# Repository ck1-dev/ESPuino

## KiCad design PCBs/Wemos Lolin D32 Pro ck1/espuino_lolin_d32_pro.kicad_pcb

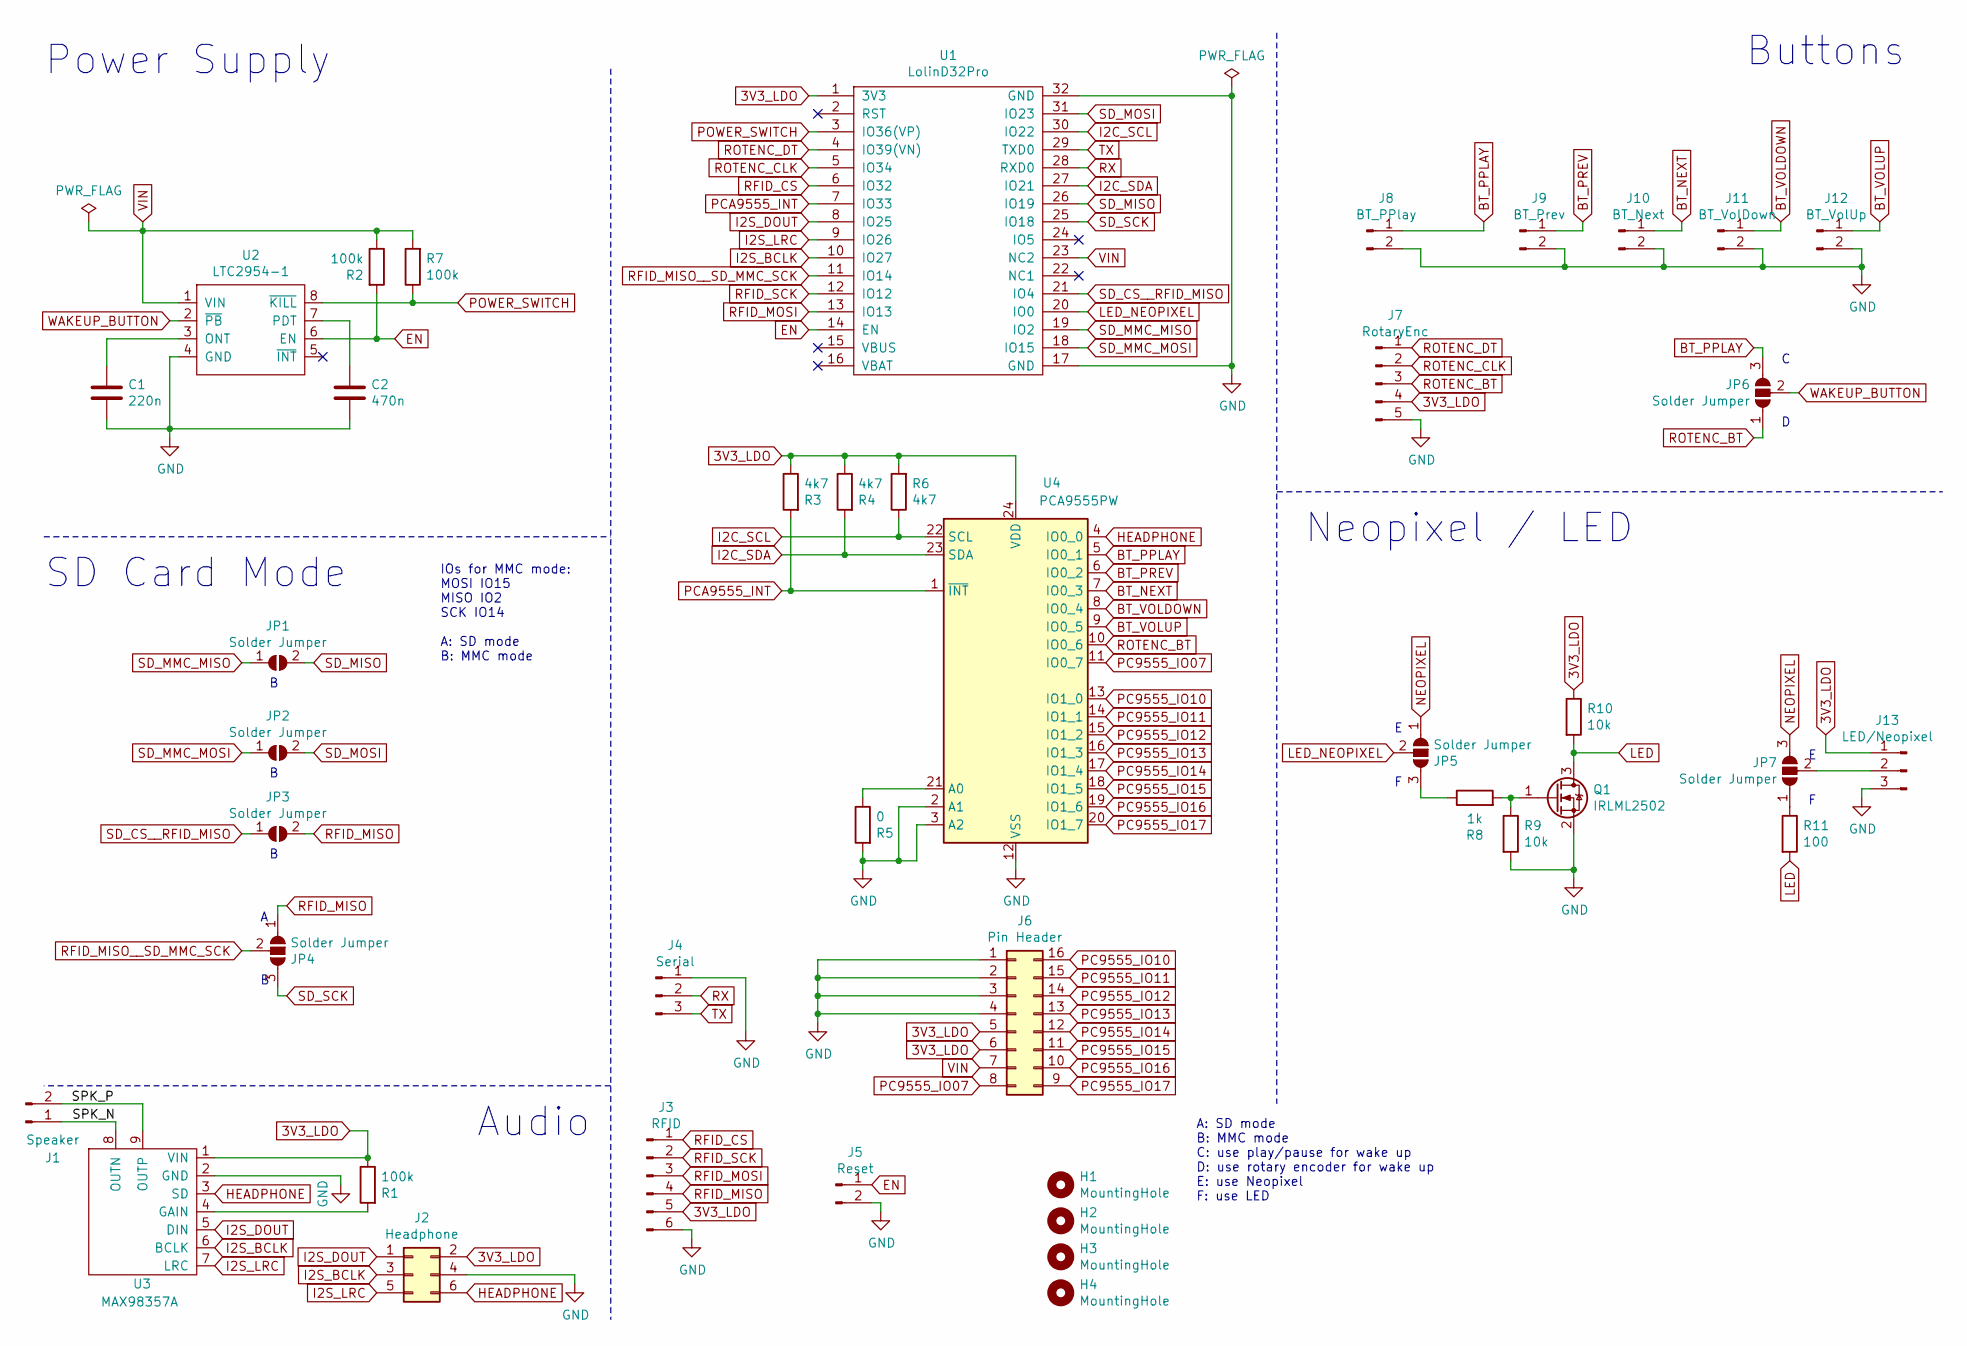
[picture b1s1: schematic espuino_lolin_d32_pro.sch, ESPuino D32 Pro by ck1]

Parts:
C1: 220n; C_0805_2012Metric_Pad1.18x1.45mm_HandSolder
C2: 470n; C_0805_2012Metric_Pad1.18x1.45mm_HandSolder
H1, H2, H3, H4: MountingHole; MountingHole_3mm
J1: Speaker; JST_PH_B2B-PH-K_1x02_P2.00mm_Vertical
J2: Headphone; IDC-Header_2x03_P2.54mm_Vertical
J3: RFID; JST_PH_B6B-PH-K_1x06_P2.00mm_Vertical
J4: Serial; PinHeader_1x03_P2.54mm_Vertical
J5: Reset; JST_PH_B2B-PH-K_1x02_P2.00mm_Vertical
J6: Pin Header; PinHeader_2x08_P2.54mm_Vertical
J7: RotaryEnc; JST_PH_B5B-PH-K_1x05_P2.00mm_Vertical
J8: BT_PPlay; JST_PH_B2B-PH-K_1x02_P2.00mm_Vertical
J9: BT_Prev; JST_PH_B2B-PH-K_1x02_P2.00mm_Vertical
J10: BT_Next; JST_PH_B2B-PH-K_1x02_P2.00mm_Vertical
J11: BT_VolDown; JST_PH_B2B-PH-K_1x02_P2.00mm_Vertical
J12: BT_VolUp; JST_PH_B2B-PH-K_1x02_P2.00mm_Vertical
J13: LED/Neopixel; JST_PH_B3B-PH-K_1x03_P2.00mm_Vertical
JP1, JP2, JP3: Solder Jumper; SolderJumper-2_P1.3mm_Open_Pad1.0x1.5mm
JP4, JP5, JP6, JP7: Solder Jumper; SolderJumper-3_P1.3mm_Open_Pad1.0x1.5mm
Q1: IRLML2502; SOT-23
R1, R2, R7: 100k; R_0805_2012Metric_Pad1.20x1.40mm_HandSolder
R3, R4, R6: 4k7; R_0805_2012Metric_Pad1.20x1.40mm_HandSolder
R5: 0; R_0805_2012Metric_Pad1.20x1.40mm_HandSolder
R8: 1k; R_0805_2012Metric_Pad1.20x1.40mm_HandSolder
R9, R10: 10k; R_0805_2012Metric_Pad1.20x1.40mm_HandSolder
R11: 100; R_0805_2012Metric_Pad1.20x1.40mm_HandSolder
U1: LolinD32Pro; Lolin_D32_PRO
U2: LTC2954-1; TSOT-23-8
U3: MAX98357A
U4: PCA9555PW; TSSOP-24_4.4x7.8mm_P0.65mm

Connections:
3V3_LDO: J2.2, J3.5, J6.5, J6.6, J7.4, J13.1, R1.1, R3.1, R4.1, R6.2, R10.1, U1.1 (3V3), U3.1 (VIN), U4.24 (VDD)
/SPK_N: J1.1, U3.8 (OUTN)
/SPK_P: J1.2, U3.9 (OUTP)
BT_NEXT: J10.1, U4.7 (IO0_3)
BT_PPLAY: J8.1, JP6.3 (B), U4.5 (IO0_1)
BT_PREV: J9.1, U4.6 (IO0_2)
BT_VOLDOWN: J11.1, U4.8 (IO0_4)
BT_VOLUP: J12.1, U4.9 (IO0_5)
EN: J5.1, R2.2, U1.14 (EN), U2.6 (EN)
GND: C1.2, C2.2, J2.4, J3.6, J4.1, J5.2, J6.1, J6.2, J6.3, J6.4, J7.5, J8.2, J9.2, J10.2, J11.2, J12.2, J13.3, Q1.2 (S), R5.2, R9.2, U1.17 (GND), U1.32 (GND), U2.4 (GND), U3.2 (GND), U4.2 (A1), U4.3 (A2), U4.12 (VSS)
HEADPHONE: J2.6, U3.3 (SD), U4.4 (IO0_0)
I2C_SCL: R6.1, U1.30 (IO22), U4.22 (SCL)
I2C_SDA: R4.2, U1.27 (IO21), U4.23 (SDA)
I2S_BCLK: J2.3, U1.10 (IO27), U3.6 (BCLK)
I2S_DOUT: J2.1, U1.8 (IO25), U3.5 (DIN)
I2S_LRC: J2.5, U1.9 (IO26), U3.7 (LRC)
LED: Q1.3 (D), R10.2, R11.2
LED_NEOPIXEL: JP5.2 (C), U1.20 (IO0)
NEOPIXEL: JP5.1 (A), JP7.3 (B)
unnamed: C1.1, U2.3 (ONT)
unnamed: C2.1, U2.7 (PDT)
unnamed: J13.2, JP7.2 (C)
unnamed: JP5.3 (B), R8.1
unnamed: JP7.1 (A), R11.1
unnamed: Q1.1 (G), R8.2, R9.1
unnamed: R1.2, U3.4 (GAIN)
unnamed: R5.1, U4.21 (A0)
PC9555_IO07: J6.8, U4.11 (IO0_7)
PC9555_IO10: J6.16, U4.13 (IO1_0)
PC9555_IO11: J6.15, U4.14 (IO1_1)
PC9555_IO12: J6.14, U4.15 (IO1_2)
PC9555_IO13: J6.13, U4.16 (IO1_3)
PC9555_IO14: J6.12, U4.17 (IO1_4)
PC9555_IO15: J6.11, U4.18 (IO1_5)
PC9555_IO16: J6.10, U4.19 (IO1_6)
PC9555_IO17: J6.9, U4.20 (IO1_7)
PCA9555_INT: R3.2, U1.7 (IO33), U4.1 (~INT)
POWER_SWITCH: R7.1, U1.3 (IO36(VP)), U2.8 (~KILL)
RFID_CS: J3.1, U1.6 (IO32)
RFID_MISO: J3.4, JP3.2 (B), JP4.1 (A)
RFID_MISO__SD_MMC_SCK: JP4.2 (C), U1.11 (IO14)
RFID_MOSI: J3.3, U1.13 (IO13)
RFID_SCK: J3.2, U1.12 (IO12)
ROTENC_BT: J7.3, JP6.1 (A), U4.10 (IO0_6)
ROTENC_CLK: J7.2, U1.5 (IO34)
ROTENC_DT: J7.1, U1.4 (IO39(VN))
RX: J4.2, U1.28 (RXD0)
SD_CS__RFID_MISO: JP3.1 (A), U1.21 (IO4)
SD_MISO: JP1.2 (B), U1.26 (IO19)
SD_MMC_MISO: JP1.1 (A), U1.19 (IO2)
SD_MMC_MOSI: JP2.1 (A), U1.18 (IO15)
SD_MOSI: JP2.2 (B), U1.31 (IO23)
SD_SCK: JP4.3 (B), U1.25 (IO18)
TX: J4.3, U1.29 (TXD0)
VIN: J6.7, R2.1, R7.2, U1.23 (NC2), U2.1 (VIN)
WAKEUP_BUTTON: JP6.2 (C), U2.2 (~PB)

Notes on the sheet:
Buttons
Power Supply
Audio
Neopixel / LED
SD Card Mode
IOs for MMC mode: MOSI IO15 MISO IO2 SCK IO14 A: SD mode B: MMC mode
A: SD mode B: MMC mode C: use play/pause for wake up D: use rotary encoder for wake up E: use Neopixel F: use LED

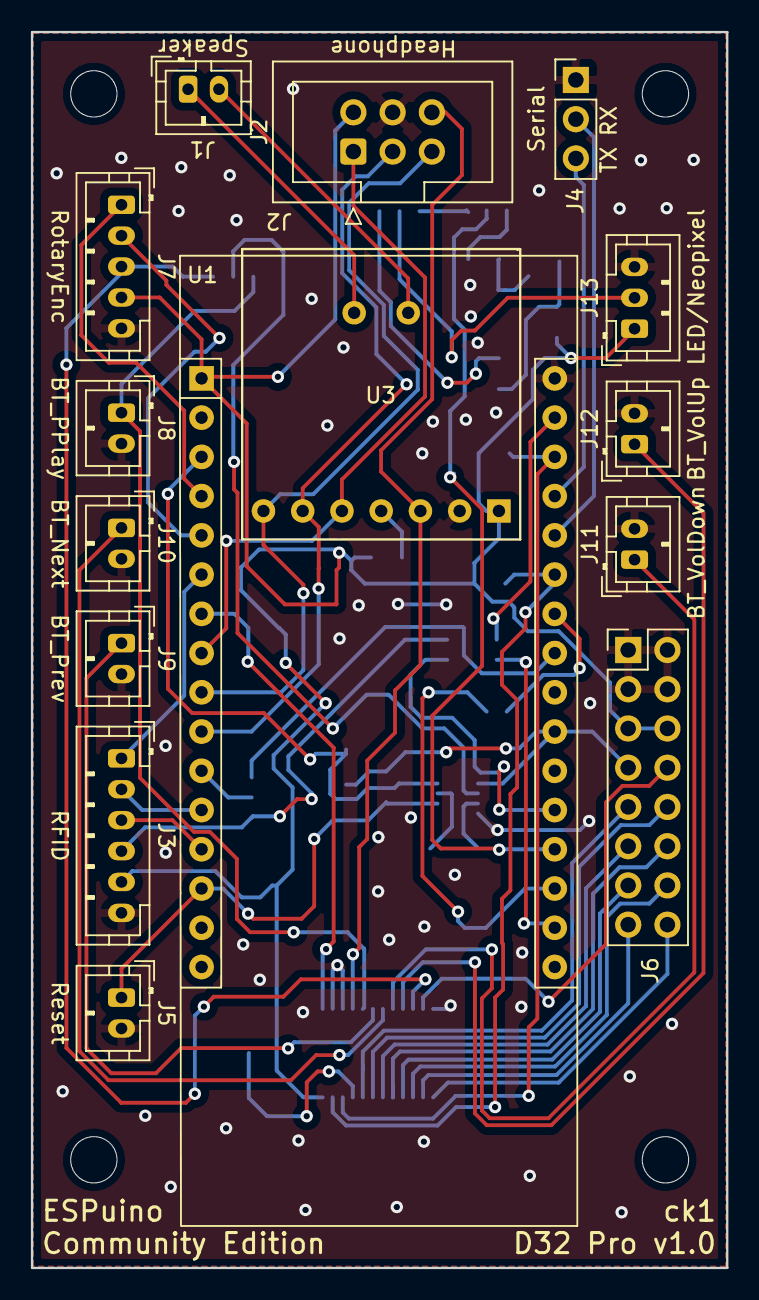
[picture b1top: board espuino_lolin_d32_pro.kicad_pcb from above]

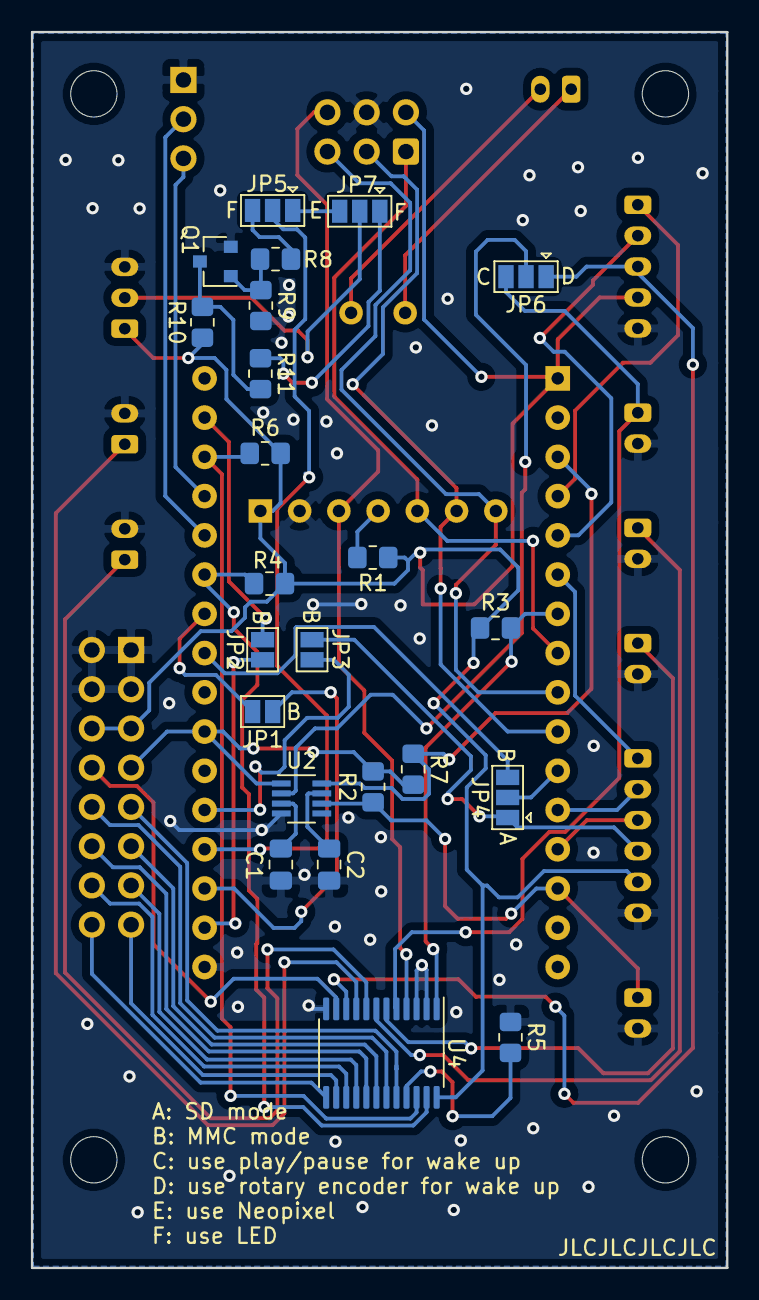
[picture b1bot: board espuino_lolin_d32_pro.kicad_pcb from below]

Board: 2 copper layers, 45.0 x 80.0 mm, 42 parts (23 on the bottom side), 56 nets.

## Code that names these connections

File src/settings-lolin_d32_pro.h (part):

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
    // RFID (via SPI)
    #define RST_PIN                         99          // Not necessary but has to be set anyway; so let's use a dummy-number
    #define RFID_CS                         32          // GPIO for chip select (RFID)
    #define RFID_MOSI                       13          // GPIO for master out slave in (RFID)
    #define RFID_MISO                       14          // GPIO for master in slave out (RFID)
    #define RFID_SCK                        12          // GPIO for clock-signal (RFID)

    #ifdef RFID_READER_TYPE_PN5180
        #define RFID_BUSY                   33          // PN5180 BUSY PIN
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        #define RFID_IRQ                    39          // PN5180 IRQ PIN (only needed for low power card detection)
    #endif
    // I2S (DAC)
    #define I2S_DOUT                        25          // Digital out (I2S)
    #define I2S_BCLK                        27          // BCLK (I2S)
    #define I2S_LRC                         26          // LRC (I2S)

    // Rotary encoder
    #ifdef USEROTARY_ENABLE
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    // Wake-up button => this also is the interrupt-pin if port-expander is enabled!
    // Please note: only RTC-GPIOs (0, 4, 12, 13, 14, 15, 25, 26, 27, 32, 33, 34, 35, 36, 39, 99) can be used! Set to 99 to DISABLE.
    // Please note #2: this button can be used as interrupt-pin for port-expander. If so, all pins connected to port-expander can wake up ESPuino.
    #define WAKEUP_BUTTON                   99 //ROTARYENCODER_BUTTON // Defines the button that is used to wake up ESPuino from deepsleep.

    // (optional) Power-control
    #define POWER                           99//5           // GPIO used to drive transistor-circuit, that switches off peripheral devices while ESP32-deepsleep
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    #endif

    // (optional) Neopixel
    #define LED_PIN                         0          // GPIO for Neopixel-signaling

    // (optinal) Headphone-detection
    #ifdef HEADPHONE_ADJUST_ENABLE
        //#define DETECT_HP_ON_HIGH                       // Per default headphones are supposed to be connected if HT_DETECT is LOW. DETECT_HP_ON_HIGH will change this behaviour to HIGH.
        #define HP_DETECT                   100          // GPIO that detects, if there's a plug in the headphone jack or not
    #endif

    // (optional) Monitoring of battery-voltage via ADC
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
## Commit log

2021-08-06 configure d32 pro
2021-08-07 adapt settings to custom pcb
2021-08-14 power-down test
2021-09-12 switch next/prev track and volume up/down
2021-09-25 add copy of d32 pro pcb
2021-10-09 make project compilable again
2021-10-09 implement simple led status
2023-01-22 force enable wifi (for Luisa's box)
2023-02-13 preparing updated original files for own d32 pcb
